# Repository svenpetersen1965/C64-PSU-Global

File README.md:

# C64-PSU-Global
A replacement PSU for the Commodore C64, which works with 230V/115V.

For using this PSU, a suitable enclosure is required. It must not be connected to 230V while 115V mains is selected.

This PSU is designed for a low price at a decent comfort and for providing a PSU that can be switched between 230V and 115V mains.

The testing of Rev. 0 is still preliminary. The PSU was successfully tested with all ASSYs, that I have (250407, 250425, 250466, 250469). The panel meter current measurement worked, but the reading of all panelmeters was off, because those seem to have a bad quality. In Rev. 1 (yet to be released), the current measurement was dropped. The jumpers for bridging the current measurement should be replaced with short wire bridges in Rev. 0.

The changes in <b>Rev. 1</b> are the dropped current measurement. The freed space was used for wider copper tracks. The complete documentation, test documents are released now. The documentation of Rev. 0 will stay incomplete, most of the Rev. 1 documentation applies to Rev. 0 as well.  

Find some info on the required cable making <a href="http://tech.guitarsite.de/cable_making.html">on my website</a>

# Case
The case is designed. At 24°C room temperature the temperature measured above the transformer reached 44°C while powering an ASSY 250425 C64. This is not critical, since the critical temperature for PLA is 55°C-60°C. In case you need to operate the power supply in higher ambient temperatures, you should consider PETG or ABS for printing or install the PSU in a metal case.

The case was designed to fit the <a href="https://github.com/svenpetersen1965/Illuminated-Commmodore-logo">illuminated Commodore Logo</a> or <a href="https://github.com/svenpetersen1965/Illuminated-64-logo">64 Logo</a> (in my repository).  

Since there is a version of the PSU for 230V only and one version that can be switched between 115V and 230V, which requires a mains voltage selector switch, there are two versions for the bottom shell.

# Prices
I have calculated the prices of May 2020.
Those prices do not include shipping fees and might differ from distributor to distributor. The prices of the items are from reichelt.de and tme.eu.

A 115V/230V type is 40,90€

A 230V only type is 35,11€

This does not incluse the 3D printed case, which might weigh 150g and take 12h to print.

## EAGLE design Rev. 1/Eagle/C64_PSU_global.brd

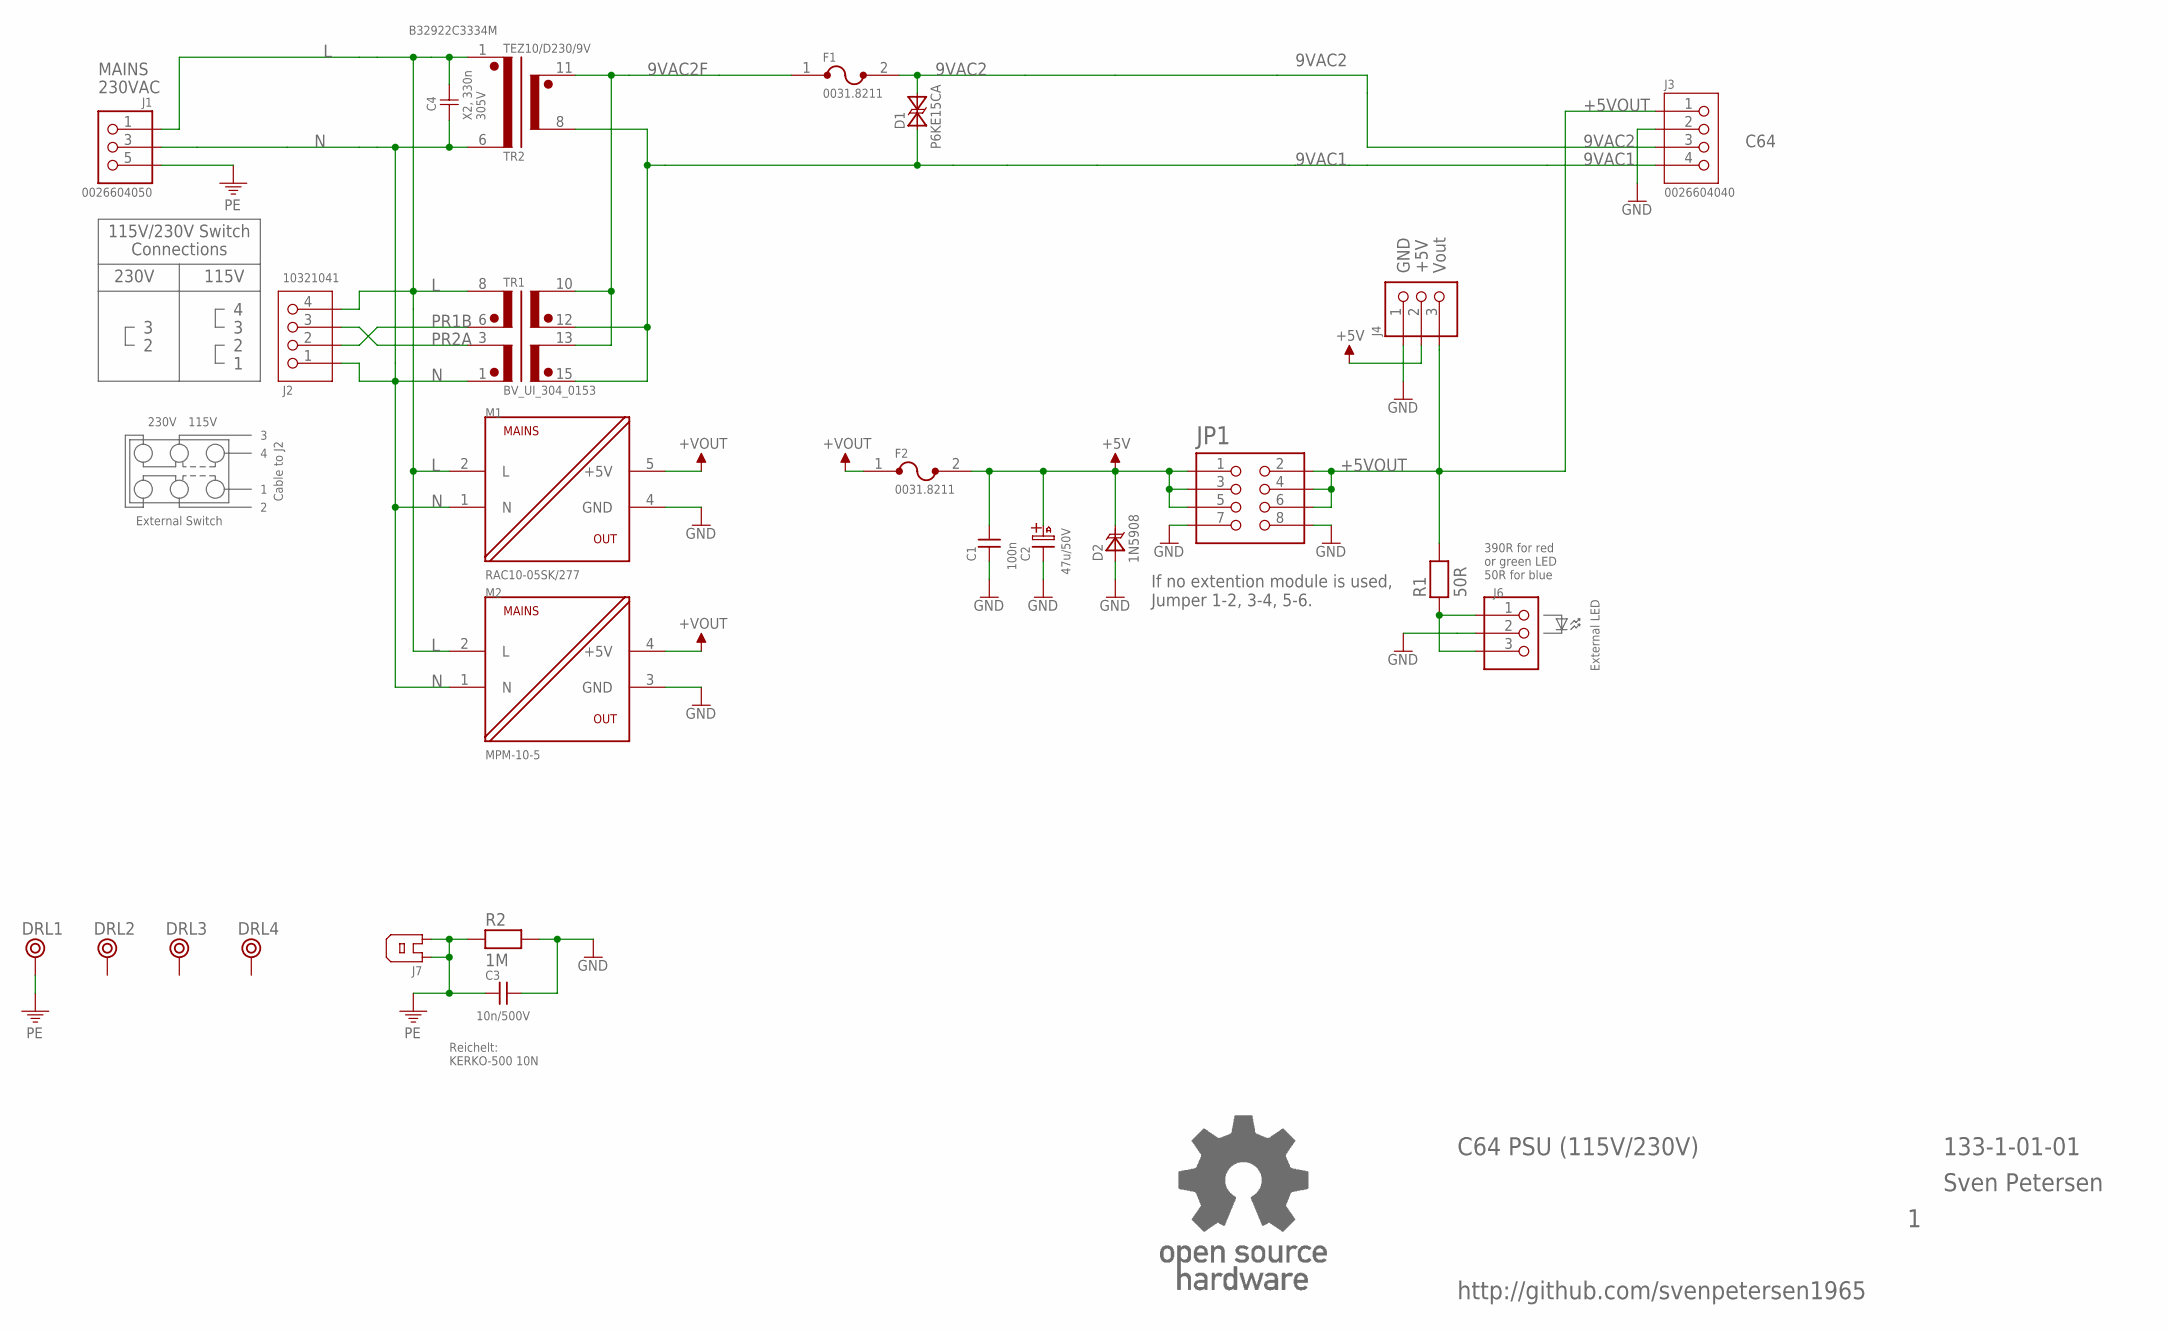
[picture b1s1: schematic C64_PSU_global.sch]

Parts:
C1: 100n; C-2,5
C2: 47u/50V; C07/2,5
C3: 10n/500V; C-5
C4: B32922C3334M; C-18X8-RM15
D1: P6KE15CA; CB417NP
D2: 1N5908; CB429
DRL1: BOHR3,5OR; BOHR3,5_OHNE_RESTRICT
DRL2, DRL3, DRL4: BOHR3,5
F1, F2: 0031.8211
J1: 0026604050; SPOX_3.96_5P3
J2: 10321041; SPOX_5.08_4P
J3: 0026604040; SPOX_3.96_4P
J4: 6410-3P
J6: PINHD-1X3; 1X03
J7: FLA6,3
JP1: PINHD-2X4; 2X04
M1: RAC10-05SK/277; RAC10-K/277
M2: MPM-10-5; MPM10
R1: 50R; R-10
R2: 1M; R-10
TR1: BV_UI_304_0153; UI30
TR2: TEZ10/D230/9V; TEZ10
U$25: OPEN_SOURCE_HW; OPENHW

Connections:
9VAC1: D1.A (A1), J3.4, TR1.12 (SEC1B), TR1.15 (SEC2B), TR2.8 (SEC11)
9VAC2: D1.K (A2), F1.2, J3.3
9VAC2F: F1.1, TR1.10 (SEC1A), TR1.13 (SEC2A), TR2.11 (SEC12)
+5V: C1.2, C2.A (+), D2.K, F2.2, J4.2, JP1.1, JP1.3, JP1.5
+5VOUT: J3.1, J4.3, JP1.2, JP1.4, JP1.6, R1.2
+VOUT: F2.1, M1.5 (+5V), M2.4 (+5V)
GND: C1.1, C2.K (-), C3.2, D2.A, J3.2, J4.1, J6.2, JP1.7, JP1.8, M1.4 (GND), M2.3 (GND), R2.2
L: C4.2, J1.1, J2.4, M1.2 (L), M2.2 (L), TR1.8 (PRI1A), TR2.1 (PRI2)
N: C4.1, J1.3 (2), J2.1, M1.1 (N), M2.1 (N), TR1.1 (PRI2B), TR2.6 (PRI1)
unnamed: J6.1, J6.3, R1.1
PE: C3.1, DRL1.P$1, J1.5 (3), J7.1, J7.2, R2.1
PR1B: J2.2, TR1.6 (PRI1B)
PR2A: J2.3, TR1.3 (PRI2A)

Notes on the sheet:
External LED
390R for red or green LED 50R for blue
Reichelt: KERKO-500 10N
If no extention module is used, Jumper 1-2, 3-4, 5-6.
+5V
GND
Vout
230VAC
X2, 330n 305V
MAINS
C64
115V/230V Switch
230V
115V
Connections
C64 PSU (115V/230V)
133-1-01-01
Sven Petersen
Cable to J2
External Switch
http://github.com/svenpetersen1965

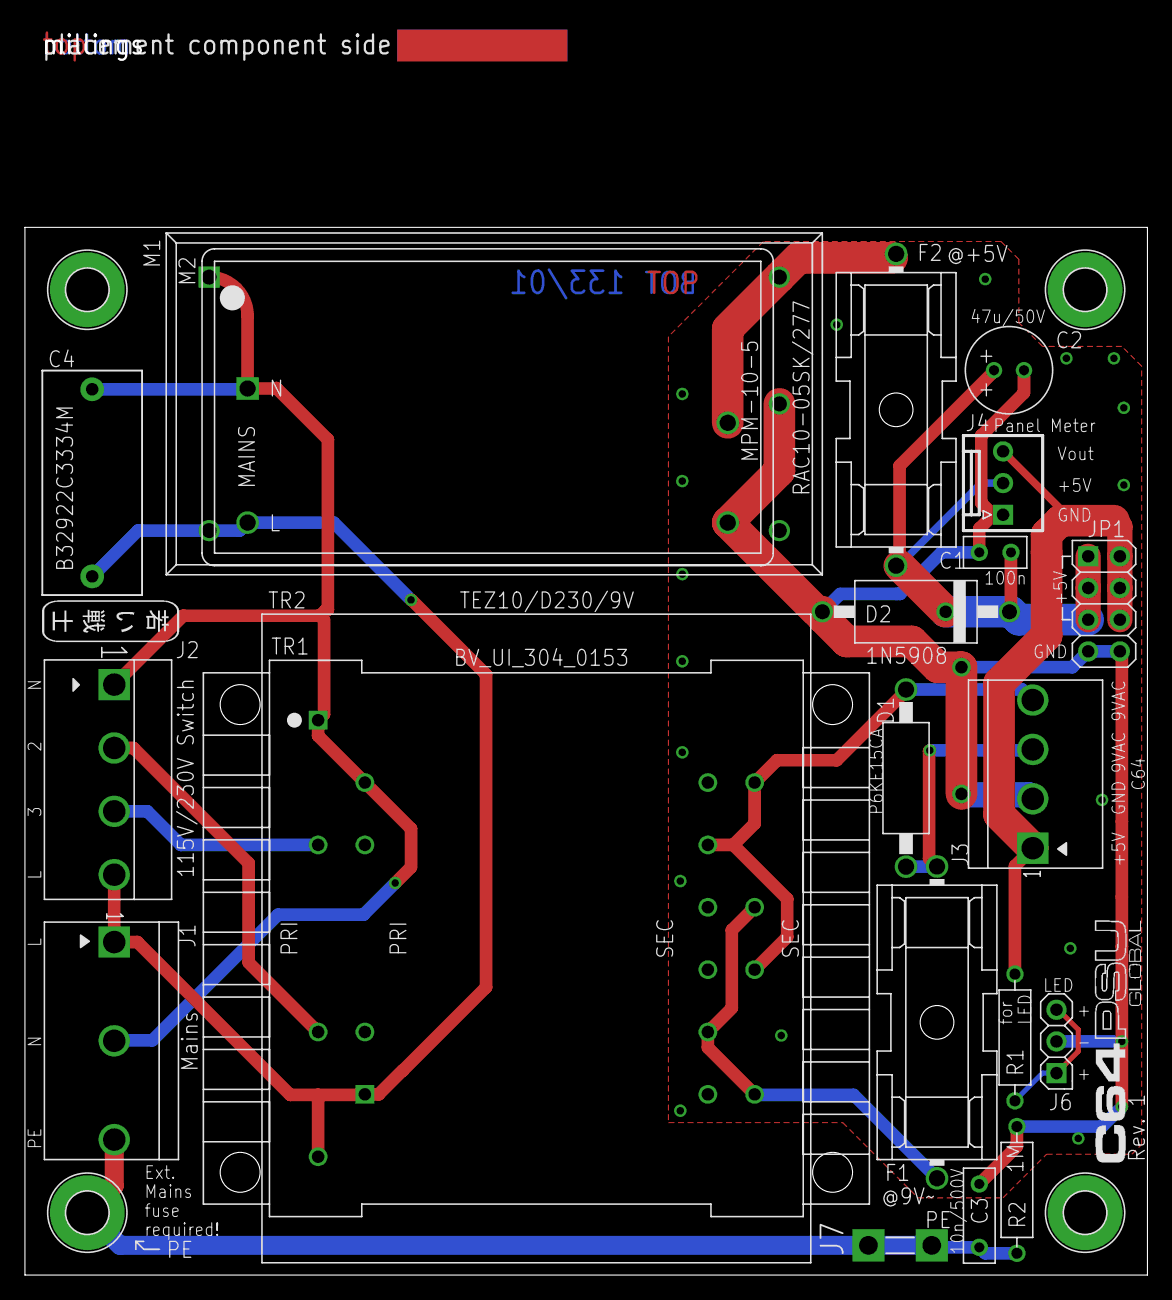
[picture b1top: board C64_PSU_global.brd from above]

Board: 2 copper layers, 90.0 x 100.2 mm, 30 parts (1 on the bottom side), 13 nets.

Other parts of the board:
U$14: PCB-TITLE/
U$20: SVEN_TAG
U$22: C64_PSU_GLOBAL
U$23: 2LAYER

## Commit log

2020-01-16 Initial release
2020-03-13 Case release
2020-04-12 Rev. 1 released
2020-04-12 Doc now with disclaimer
2020-05-26 Corrected BOM and added price calculation
2020-08-10 Silk Screen Update
2022-02-26 Gerbers removed
2022-02-27 Outdated gerbers removed
